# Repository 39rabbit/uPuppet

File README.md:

# uPuppet
fabacademy2015 final project

What are in here

*Hallsens: the program in input device
*Input.app, Output.app : software applications
*OutputServos : the program in output deivce.
*stl files are inside of output device.
*3dm files are design for output device and it's also the cutting design for fabrics.

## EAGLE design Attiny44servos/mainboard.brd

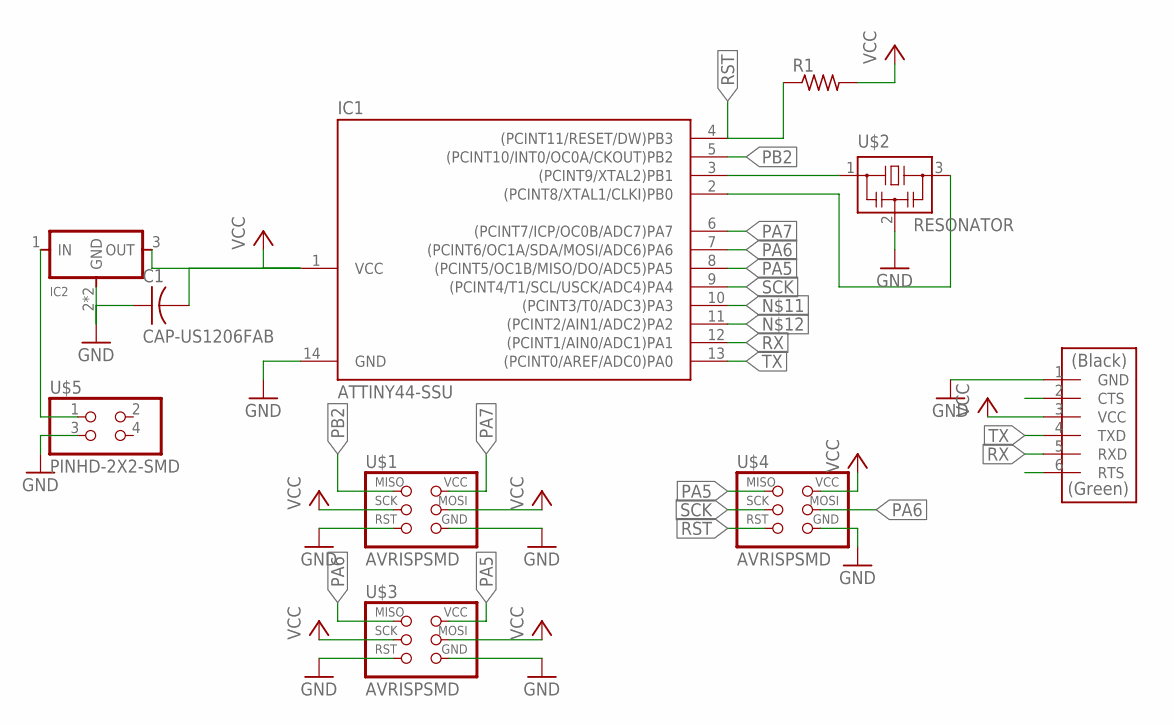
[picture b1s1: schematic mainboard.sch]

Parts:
C1: CAP-US1206FAB; C1206FAB
IC1: ATTINY44-SSU; SOIC14
IC2: REGULATORSOT223; SOT223
R1: RES-US1206FAB; R1206FAB
U$1, U$3, U$4: AVRISPSMD; 2X03SMD
U$2: RESONATOR; EFOBM
U$5: PINHD-2X2-SMD; 2X02SMD
U$6: FTDI-SMD-HEADER; 1X06SMD

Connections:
GND: C1.1, IC1.14 (GND), IC2.2 (GND), IC2.4 (GND), U$1.5 (RST), U$1.6 (GND), U$2.2, U$3.5 (RST), U$3.6 (GND), U$4.6 (GND), U$5.3, U$6.1 (GND)
unnamed: IC2.1 (IN), U$5.1
unnamed: IC1.3 ((PCINT9/XTAL2)PB1), U$2.1
PA5: IC1.8 ((PCINT5/OC1B/MISO/DO/ADC5)PA5), U$3.2 (VCC), U$4.1 (MISO)
PA6: IC1.7 ((PCINT6/OC1A/SDA/MOSI/ADC6)PA6), U$3.1 (MISO), U$4.4 (MOSI)
PA7: IC1.6 ((PCINT7/ICP/OC0B/ADC7)PA7), U$1.2 (VCC)
PA': IC1.2 ((PCINT8/XTAL1/CLKI)PB0), U$2.3
PB2: IC1.5 ((PCINT10/INT0/OC0A/CKOUT)PB2), U$1.1 (MISO)
RST: IC1.4 ((PCINT11/RESET/DW)PB3), R1.1, U$4.5 (RST)
RX: IC1.12 ((PCINT1/AIN0/ADC1)PA1), U$6.5 (RXD)
SCK: IC1.9 ((PCINT4/T1/SCL/USCK/ADC4)PA4), U$4.3 (SCK)
TX: IC1.13 ((PCINT0/AREF/ADC0)PA0), U$6.4 (TXD)
VCC: C1.2, IC1.1 (VCC), IC2.3 (OUT), R1.2, U$1.3 (SCK), U$1.4 (MOSI), U$3.3 (SCK), U$3.4 (MOSI), U$4.2 (VCC), U$6.3 (VCC)

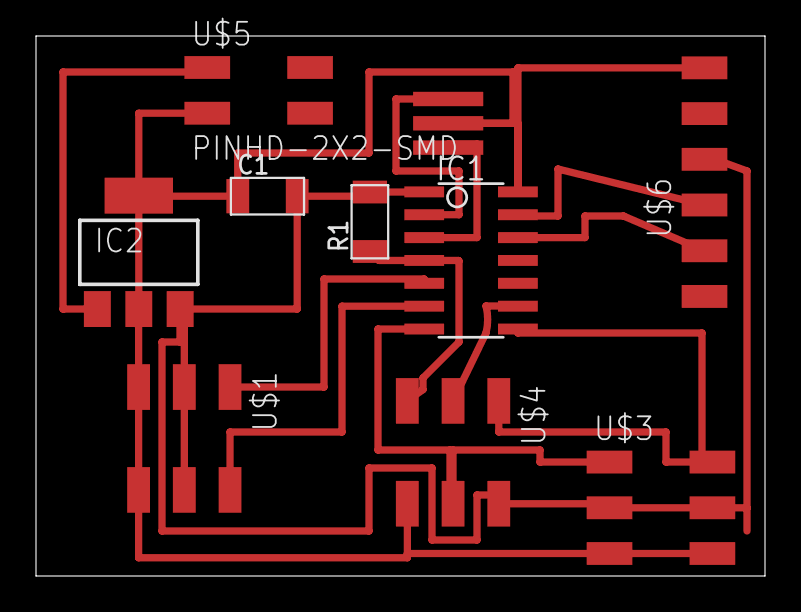
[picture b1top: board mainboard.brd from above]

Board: 2 copper layers, 40.5 x 30.0 mm, 10 parts (0 on the bottom side), 13 nets.

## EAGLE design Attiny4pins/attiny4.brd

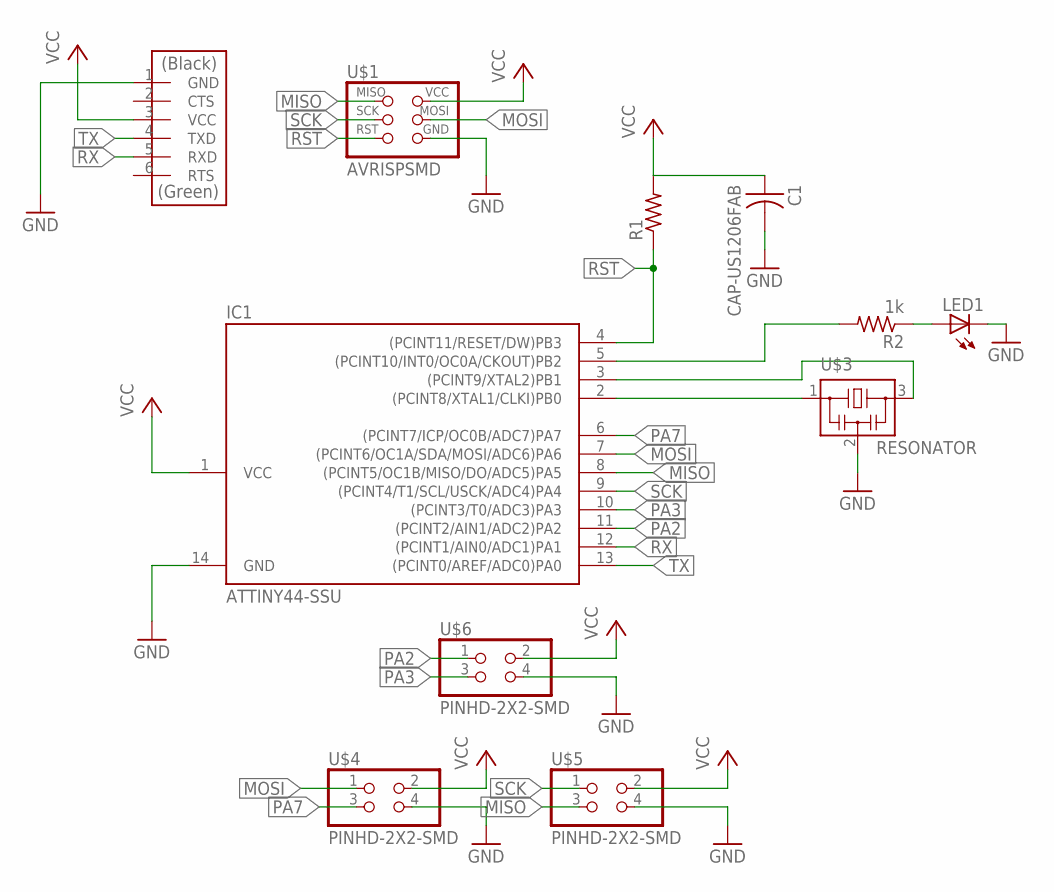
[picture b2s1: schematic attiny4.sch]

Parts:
C1: CAP-US1206FAB; C1206FAB
IC1: ATTINY44-SSU; SOIC14
LED1: LEDSML1206; SML1206
R1: RES-US1206FAB; R1206FAB
R2: 1k; R1206FAB
U$1: AVRISPSMD; 2X03SMD
U$2: FTDI-SMD-HEADER; 1X06SMD
U$3: RESONATOR; EFOBM
U$4, U$5, U$6: PINHD-2X2-SMD; 2X02SMD

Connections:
GND: C1.2, IC1.14 (GND), LED1.C, U$1.6 (GND), U$2.1 (GND), U$3.2, U$4.4, U$5.4, U$6.4
MISO: IC1.8 ((PCINT5/OC1B/MISO/DO/ADC5)PA5), U$1.1 (MISO), U$5.3
MOSI: IC1.7 ((PCINT6/OC1A/SDA/MOSI/ADC6)PA6), U$1.4 (MOSI), U$4.1
unnamed: LED1.A, R2.1
unnamed: IC1.3 ((PCINT9/XTAL2)PB1), U$3.3
unnamed: IC1.2 ((PCINT8/XTAL1/CLKI)PB0), U$3.1
PA2: IC1.11 ((PCINT2/AIN1/ADC2)PA2), U$6.1
PA3: IC1.10 ((PCINT3/T0/ADC3)PA3), U$6.3
PA7: IC1.6 ((PCINT7/ICP/OC0B/ADC7)PA7), U$4.3
PB2: IC1.5 ((PCINT10/INT0/OC0A/CKOUT)PB2), R2.2
RST: IC1.4 ((PCINT11/RESET/DW)PB3), R1.1, U$1.5 (RST)
RX: IC1.12 ((PCINT1/AIN0/ADC1)PA1), U$2.5 (RXD)
SCK: IC1.9 ((PCINT4/T1/SCL/USCK/ADC4)PA4), U$1.3 (SCK), U$5.1
TX: IC1.13 ((PCINT0/AREF/ADC0)PA0), U$2.4 (TXD)
VCC: C1.1, IC1.1 (VCC), R1.2, U$1.2 (VCC), U$2.3 (VCC), U$4.2, U$5.2, U$6.2

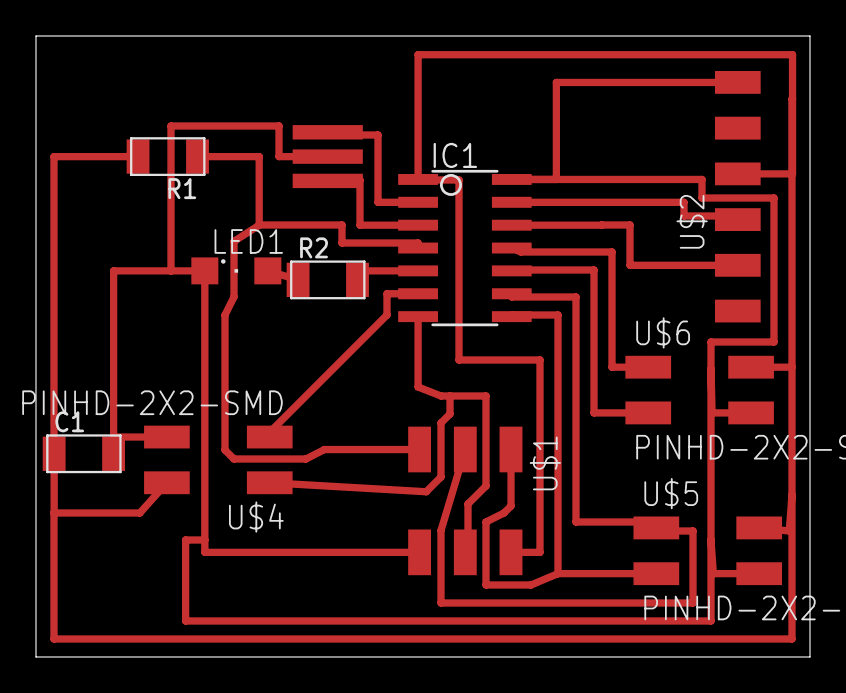
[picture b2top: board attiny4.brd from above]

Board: 2 copper layers, 43.0 x 34.5 mm, 11 parts (0 on the bottom side), 15 nets.

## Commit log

2015-06-16 /Users/hisatsunetaichi/Documents/Git/upuppet_git/Input.app/Contents/Data/Managed/etc/mono/2.0/machine.config/Users/hisatsunetaichi/Documents/Git/upuppet_git/Hallsens/Hallsens.ino /Users/hisatsunetaic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
2015-06-30 no message
